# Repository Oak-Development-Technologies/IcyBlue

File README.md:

# IcyBlue Feather FPGA Development Board

<image src="https://github.com/Oak-Development-Technologies/IcyBlue/blob/main/Images/IMG_2196.jpg">

Welcome to the home of the IcyBlue Feather, an FPGA based development board designed to be integrated into the Adafruit Feather ecosystem of Feathers and Feather Wings.

The goal of this repository is to be the single source of truth for the IcyBlue Feather. Containing all the relevant articles including images, schematics, usage examples, board files, and other important documentation.

Questions? Email [hello@oakdev.tech](mailto:hello@oakdev.tech)

### Documentation ###

All documentation can be found under the [Documentation](https://github.com/Oak-Development-Technologies/IcyBlue/tree/main/Documentation) directory of this repository. This will include data sheets, usage guides, application notes, errata, and other important documents.

Documentation quick links:
* Data sheet: [IcyBlue Overview Data Sheet](https://github.com/Oak-Development-Technologies/IcyBlue/blob/main/Documentation/IcyBlue%20Feather%20V2%20Datasheet%20rev1a.docx)
* Board files: [EagleCAD Board Files](https://github.com/Oak-Development-Technologies/IcyBlue/blob/main/Documentation/Lattice%20FPGA%20standard%20feather%20wing.kicad_pcb)
* Schematic files: [EagleCAD Schematic Files](https://github.com/Oak-Development-Technologies/IcyBlue/blob/main/Documentation/Lattice%20FPGA%20standard%20feather%20wing.kicad_sch)

### Schematic ###

Represented below is the Rev 1a schematic. This is the current production schematic for the IcyBlue Feather. If major hardware changes are added, additional labeled schematic images can be found here and in the [documentation directory](https://github.com/Oak-Development-Technologies/IcyBlue/tree/main/Documentation).

<image src="https://github.com/Oak-Development-Technologies/IcyBlue/blob/main/Images/IcyBlue%20Schematic.png">

### Usage Examples ###

All usage examples including the RGB sequence example that ships with the board can be found in the [examples repository](https://github.com/skerr92/ice5lp4k_examples).

Examples Quick Links:
* [RGB Blink](https://github.com/skerr92/ice5lp4k_examples/tree/master/leds)
* [DSP Example](https://github.com/skerr92/ice5lp4k_examples/tree/master/dsp)
* [RGB Rainbow Chase](https://github.com/Oak-Development-Technologies/ice40_rgb_rainbow_chase)

### Errata ###

Any Errate for the IcyBlue Feather will be linked below with the specific dates and errata version.

### Additional Information ###

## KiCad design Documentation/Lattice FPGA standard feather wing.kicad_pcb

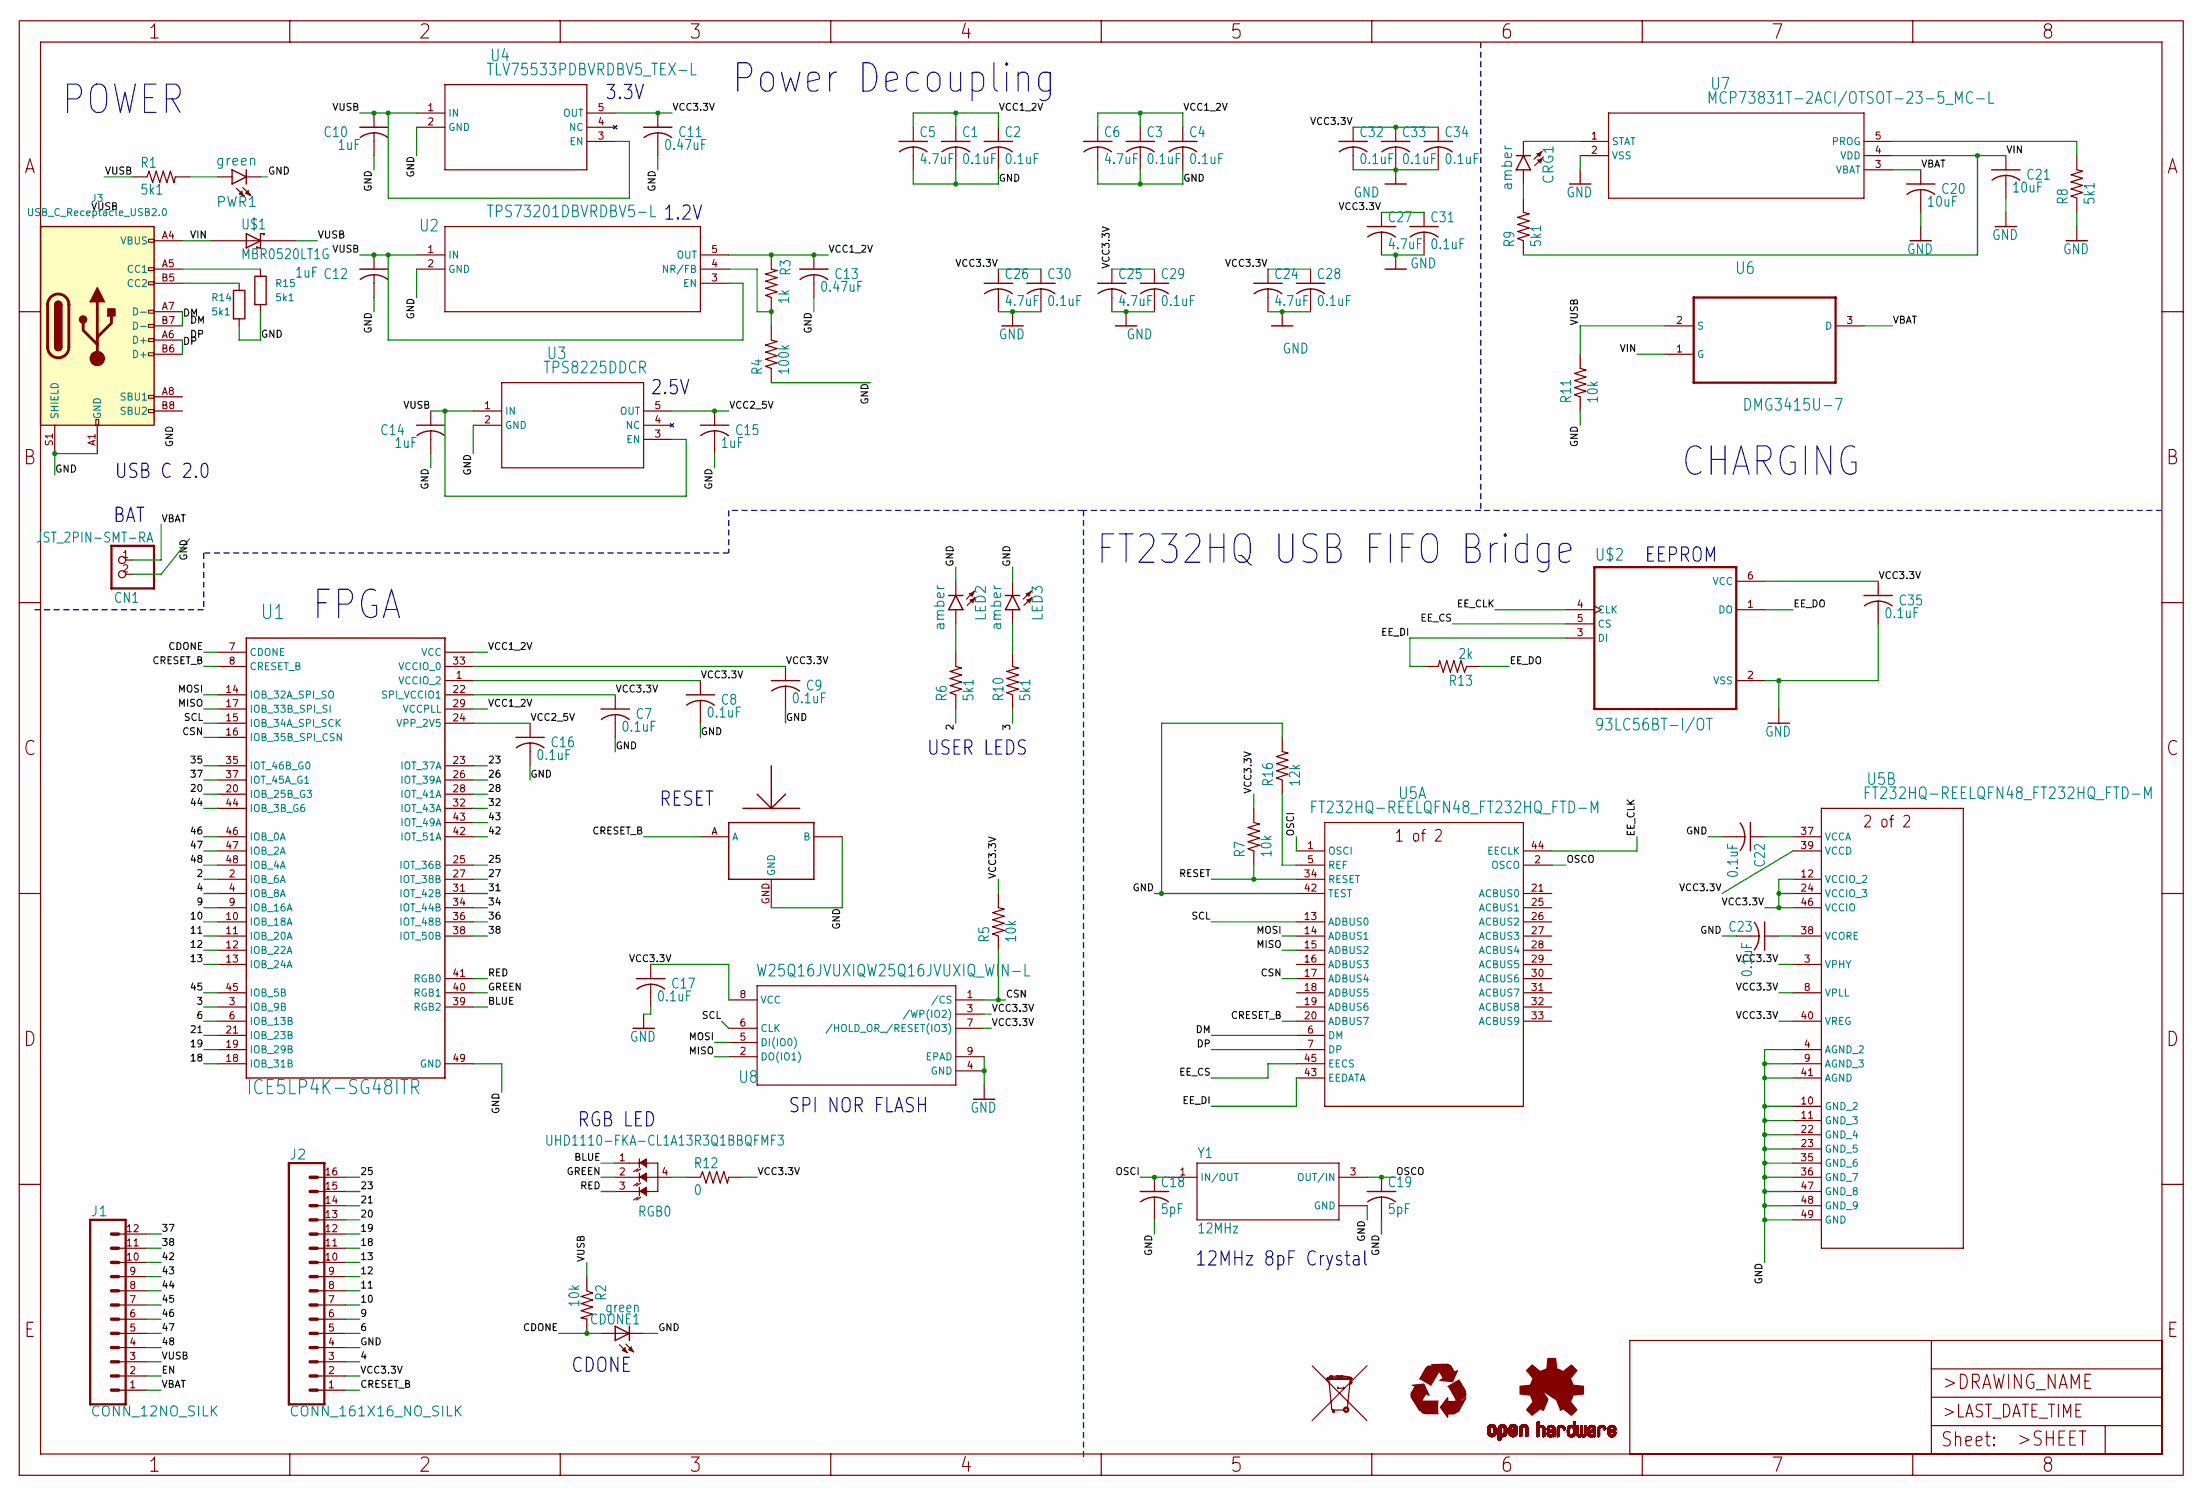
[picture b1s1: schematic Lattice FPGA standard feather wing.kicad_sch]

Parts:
C1, C2, C3, C4, C7, C8, C9, C16, C17, C22, C23, C28, C29, C30, C31, C32, C33, C34, C35: 0.1uF; C0402
C5, C6, C24, C25, C26, C27: 4.7uF; C0603
C10, C12, C14, C15: 1uF; C0402
C11, C13: 0.47uF; C0402
C18, C19: 5pF; C0402
C20, C21: 10uF; C0603
CDONE1: green; CHIP-LED0603
CN1: JST_2PIN-SMT-RA; JST-PH-2-SMT-RA
CRG1: amber; LED-0603
J1: CONN_12NO_SILK; 1X12_NO_SILK
J2: CONN_161X16_NO_SILK; 1X16_NO_SILK
J3: USB_C_Receptacle_USB2.0; USB_C_Receptacle_GCT_USB4105-xx-A_16P_TopMnt_Horizontal
LED2, LED3: amber; LED-0603
LOGO1: OSHW-LOGOS; OSHW-LOGO-S
PWR1: green; LED-0603
R1, R6, R8, R9, R10: 5k1; R0402
R2, R5, R7, R11: 10k; R0402
R3: 1k; R0402
R4: 100k; R0402
R12: 0; R0603
R13: 2k; R0402
R14, R15: 5k1; R_0402_1005Metric
R16: 12k; R0402
RGB0: UHD1110-FKA-CL1A13R3Q1BBQFMF3; LED_UHD1110-FKA-CL1A13R3Q1BBQFMF3
U1: ICE5LP4K-SG48ITR; QFN50P700X700X100-49N
U2: TPS73201DBVRDBV5-L; DBV5-L
U3: TPS8225DDCR; DBV5_TEX-L
U4: TLV75533PDBVRDBV5_TEX-L; DBV5_TEX-L
U5: FT232HQ-REELQFN48_FT232HQ_FTD-M; QFN48_FT232HQ_FTD-M
U6: DMG3415U-7; SOT95P240X105-3N
U7: MCP73831T-2ACI/OTSOT-23-5_MC-L; SOT-23-5_MC-L
U8: W25Q16JVUXIQW25Q16JVUXIQ_WIN-L; W25Q16JVUXIQ_WIN-L
U$1: MBR0520LT1G; SOD3716X117(SOD-123)
U$2: 93LC56BT-I/OT; SOT95P280X145-6N
U$3: SOF-232HST; 3.3X2.9
Y1: 12MHz; XTAL_ECS-480-10-37-JTN-TR

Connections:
/2: R6.1, U1.2 (IOB_6A)
/3: R10.1, U1.3 (IOB_9B)
/4: J2.3, U1.4 (IOB_8A)
/6: J2.5, U1.6 (IOB_13B)
/9: J2.6, U1.9 (IOB_16A)
/10: J2.7, U1.10 (IOB_18A)
/11: J2.8, U1.11 (IOB_20A)
/12: J2.9, U1.12 (IOB_22A)
/13: J2.10, U1.13 (IOB_24A)
/18: J2.11, U1.18 (IOB_31B)
/19: J2.12, U1.19 (IOB_29B)
/20: J2.13, U1.20 (IOB_25B_G3)
/21: J2.14, U1.21 (IOB_23B)
/23: J2.15, U1.23 (IOT_37A)
/25: J2.16, U1.25 (IOT_36B)
/26: U1.26 (IOT_39A)
/27: U1.27 (IOT_38B)
/28: U1.28 (IOT_41A)
/31: U1.31 (IOT_42B)
/32: U1.32 (IOT_43A)
/34: U1.34 (IOT_44B)
/35: U1.35 (IOT_46B_G0)
/36: U1.36 (IOT_48B)
/37: J1.12, U1.37 (IOT_45A_G1)
/38: J1.11, U1.38 (IOT_50B)
/42: J1.10, U1.42 (IOT_51A)
/43: J1.9, U1.43 (IOT_49A)
/44: J1.8, U1.44 (IOB_3B_G6)
/45: J1.7, U1.45 (IOB_5B)
/46: J1.6, U1.46 (IOB_0A)
/47: J1.5, U1.47 (IOB_2A)
/48: J1.4, U1.48 (IOB_4A)
/BLUE: RGB0.1 (BLUE), U1.39 (RGB2)
/CDONE: CDONE1.A, R2.2, U1.7 (CDONE)
/CRESET_B: J2.1, U1.8 (CRESET_B), U5.20 (ADBUS7), U$3.A
/CSN: R5.1, U1.16 (IOB_35B_SPI_CSN), U5.17 (ADBUS4), U8.1 (/CS)
/DM: J3.A7 (D-), J3.B7 (D-), U5.6 (DM)
/DP: J3.A6 (D+), J3.B6 (D+), U5.7 (DP)
/EE_CLK: U5.44 (EECLK), U$2.4 (CLK)
/EE_CS: U5.45 (EECS), U$2.5 (CS)
/EE_DI: R13.2, U5.43 (EEDATA), U$2.3 (DI)
/EE_DO: R13.1, U$2.1 (DO)
/EN: J1.2
/GREEN: RGB0.2 (GREEN), U1.40 (RGB1)
/MISO: U1.17 (IOB_33B_SPI_SI), U5.15 (ADBUS2), U8.2 (DO(IO1))
/MOSI: U1.14 (IOB_32A_SPI_SO), U5.14 (ADBUS1), U8.5 (DI(IO0))
/OSCI: C18.1, U5.1 (OSCI), Y1.1 (IN/OUT)
/OSCO: C19.1, U5.2 (OSCO), Y1.3 (OUT/IN)
/RED: RGB0.3 (RED), U1.41 (RGB0)
/RESET: R7.1, U5.34 (RESET)
/SCL: U1.15 (IOB_34A_SPI_SCK), U5.13 (ADBUS0), U8.6 (CLK)
/VBAT: C20.1, CN1.1 (2), J1.1, U6.3 (D), U7.3 (VBAT)
/VCC1_2V: C1.1, C2.1, C3.1, C4.1, C5.1, C6.1, C13.1, R3.2, U1.5 (VCC), U1.29 (VCCPLL), U1.30 (VCC), U2.5 (OUT)
/VCC2_5V: C15.1, C16.1, U1.24 (VPP_2V5), U3.5 (OUT)
/VCC3.3V: C7.1, C8.1, C9.1, C11.1, C17.1, C24.1, C25.1, C26.1, C27.1, C28.1, C29.1, C30.1, C31.1, C32.1, C33.1, C34.1, C35.1, J2.2, R5.2, R7.2, R12.2, U1.1 (VCCIO_2), U1.22 (SPI_VCCIO1), U1.33 (VCCIO_0), U4.5 (OUT), U5.3 (VPHY), U5.8 (VPLL), U5.12 (VCCIO_2), U5.24 (VCCIO_3), U5.39 (VCCD), U5.40 (VREG), U5.46 (VCCIO), U8.3 (/WP(IO2)), U8.7 (/HOLD_OR_/RESET(IO3)), U8.8 (VCC), U$2.6 (VCC)
/VIN: C21.1, J3.A4 (VBUS), J3.A9 (VBUS), J3.B4 (VBUS), J3.B9 (VBUS), R9.1, U6.1 (G), U7.4 (VDD), U$1.2 (A)
/VUSB: C10.1, C12.1, C14.1, J1.3, R1.1, R2.1, R11.2, U2.1 (IN), U2.3 (EN), U3.1 (IN), U3.3 (EN), U4.1 (IN), U4.3 (EN), U6.2 (S), U$1.1 (C)
GND: C1.2, C2.2, C3.2, C4.2, C5.2, C6.2, C7.2, C8.2, C9.2, C10.2, C11.2, C12.2, C13.2, C14.2, C15.2, C16.2, C17.2, C18.2, C19.2, C20.2, C21.2, C22.2, C23.2, C24.2, C25.2, C26.2, C27.2, C28.2, C29.2, C30.2, C31.2, C32.2, C33.2, C34.2, C35.2, CDONE1.C, CN1.2 (1), J2.4, J3.A1 (GND), J3.A12 (GND), J3.B1 (GND), J3.B12 (GND), J3.S1 (SHIELD), LED2.C, LED3.C, PWR1.C, R4.1, R8.1, R11.1, R14.2, R15.2, R16.2, U1.49 (GND), U2.2 (GND), U3.2 (GND), U4.2 (GND), U5.4 (AGND_2), U5.9 (AGND_3), U5.10 (GND_2), U5.11 (GND_3), U5.22 (GND_4), U5.23 (GND_5), U5.35 (GND_6), U5.36 (GND_7), U5.41 (AGND), U5.42 (TEST), U5.47 (GND_8), U5.48 (GND_9), U5.49 (GND), U7.2 (VSS), U8.4 (GND), U8.9 (EPAD), U$2.2 (VSS), U$3.B, U$3.B2 (B), U$3.B3 (B), U$3.GND, Y1.2 (GND), Y1.4 (GND)
unnamed: CRG1.A, R9.2
unnamed: J3.A5 (CC1), R15.1
unnamed: J3.B5 (CC2), R14.1
unnamed: LED2.A, R6.2
unnamed: LED3.A, R10.2
unnamed: PWR1.A, R1.2
unnamed: R12.1, RGB0.4 (ANODE)
unnamed: R3.1, R4.2, U2.4 (NR/FB)
unnamed: R16.1, U5.5 (REF)
unnamed: C22.1, U5.37 (VCCA)
unnamed: C23.1, U5.38 (VCORE)
unnamed: R8.2, U7.5 (PROG)
unnamed: CRG1.C, U7.1 (STAT)

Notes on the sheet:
CHARGING
FPGA
RGB LED
3.3V
SPI NOR FLASH
1.2V
2.5V
BAT
EEPROM
RESET
CDONE
USER LEDS
POWER
FT232HQ USB FIFO Bridge
Power Decoupling
12MHz 8pF Crystal
USB C 2.0

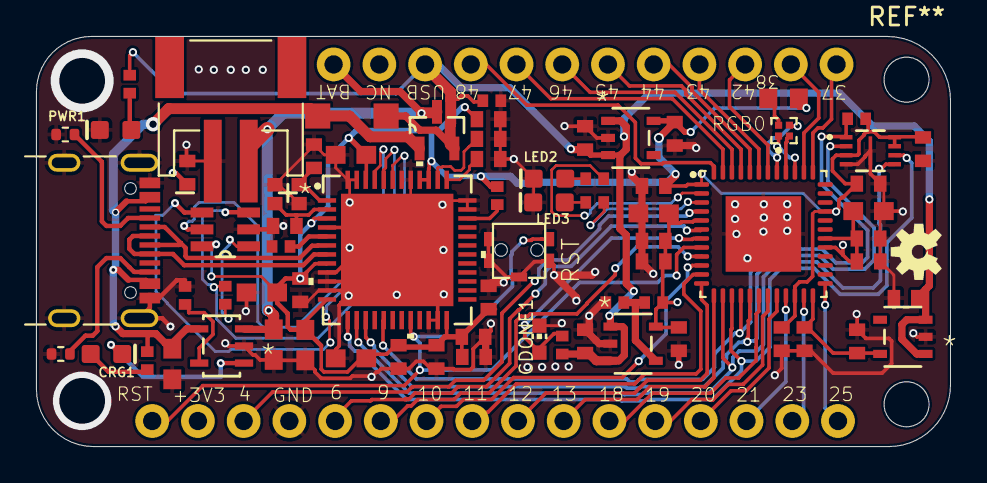
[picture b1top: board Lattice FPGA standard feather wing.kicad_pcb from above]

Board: 4 copper layers, 50.8 x 22.8 mm, 74 parts (0 on the bottom side), 62 nets.

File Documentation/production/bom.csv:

Designator,Footprint,Quantity,Value,LCSC Part #
"C1, C16, C17, C2, C22, C23, C28, C29, C3, C30, C31, C32, C33, C34, C35, C4, C7, C8, C9",C0402,19,0.1uF,
"C10, C12, C14, C15",C0402,4,1uF,
"C11, C13",C0402,2,0.47uF,
"C18, C19",C0402,2,5pF,
"C20, C21",C0603,2,10uF,
"C24, C25, C26, C27, C5, C6",C0603,6,4.7uF,
CDONE1,CHIP-LED0603,1,green,
CN1,JST-PH-2-SMT-RA,1,JST_2PIN-SMT-RA,
"CRG1, LED2, LED3",LED-0603,3,amber,
J1,1X12_NO_SILK,1,CONN_12NO_SILK,
J2,1X16_NO_SILK,1,CONN_161X16_NO_SILK,
J3,USB_C_Receptacle_GCT_USB4105-xx-A_16P_TopMnt_Horizontal,1,USB_C_Receptacle_USB2.0,
LOGO1,OSHW-LOGO-S,1,OSHW-LOGOS,
PWR1,LED-0603,1,green,
"R1, R10, R6, R8, R9",R0402,5,5k1,
"R11, R2, R5, R7",R0402,4,10k,
R12,R0603,1,0,
R13,R0402,1,2k,
"R14, R15",0402,2,5k1,
R16,R0402,1,12k,
R3,R0402,1,1k,
R4,R0402,1,100k,
RGB0,LED_UHD1110-FKA-CL1A13R3Q1BBQFMF3,1,UHD1110-FKA-CL1A13R3Q1BBQFMF3,
U$1,SOD3716X117(SOD-123),1,MBR0520LT1G,
U$2,SOT95P280X145-6N,1,93LC56BT-I/OT,
U$3,3.3X2.9,1,SOF-232HST,
U1,QFN50P700X700X100-49N,1,ICE5LP4K-SG48ITR,
U2,DBV5-L,1,TPS73201DBVRDBV5-L,
U3,DBV5_TEX-L,1,TPS8225DDCR,
U4,DBV5_TEX-L,1,TLV75533PDBVRDBV5_TEX-L,
U5,QFN48_FT232HQ_FTD-M,1,FT232HQ-REELQFN48_FT232HQ_FTD-M,
U6,SOT95P240X105-3N,1,DMG3415U-7,
U7,SOT-23-5_MC-L,1,MCP73831T-2ACI/OTSOT-23-5_MC-L,
U8,W25Q16JVUXIQ_WIN-L,1,W25Q16JVUXIQW25Q16JVUXIQ_WIN-L,
Y1,XTAL_ECS-480-10-37-JTN-TR,1,12MHz,

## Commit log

2023-08-05 new images of IcyBlue Rev2
2023-08-05 Update LICENSE
2024-04-05 adding V2 overview Data sheet
2024-04-05 Add V2 product images
2024-04-05 Partial Update to README.md
2024-04-05 add new schematics, JLCPCB manufacturing files etc
2024-04-05 add schematic picture
2024-04-05 Other Updates for README.md
